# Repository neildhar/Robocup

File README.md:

Robocup
=======

Contains code for arduino robocup Robot as well as schematics for the custom PCBs.

Please ensure that you leave sensible messages when you commit so that other people don't have to decipher them.

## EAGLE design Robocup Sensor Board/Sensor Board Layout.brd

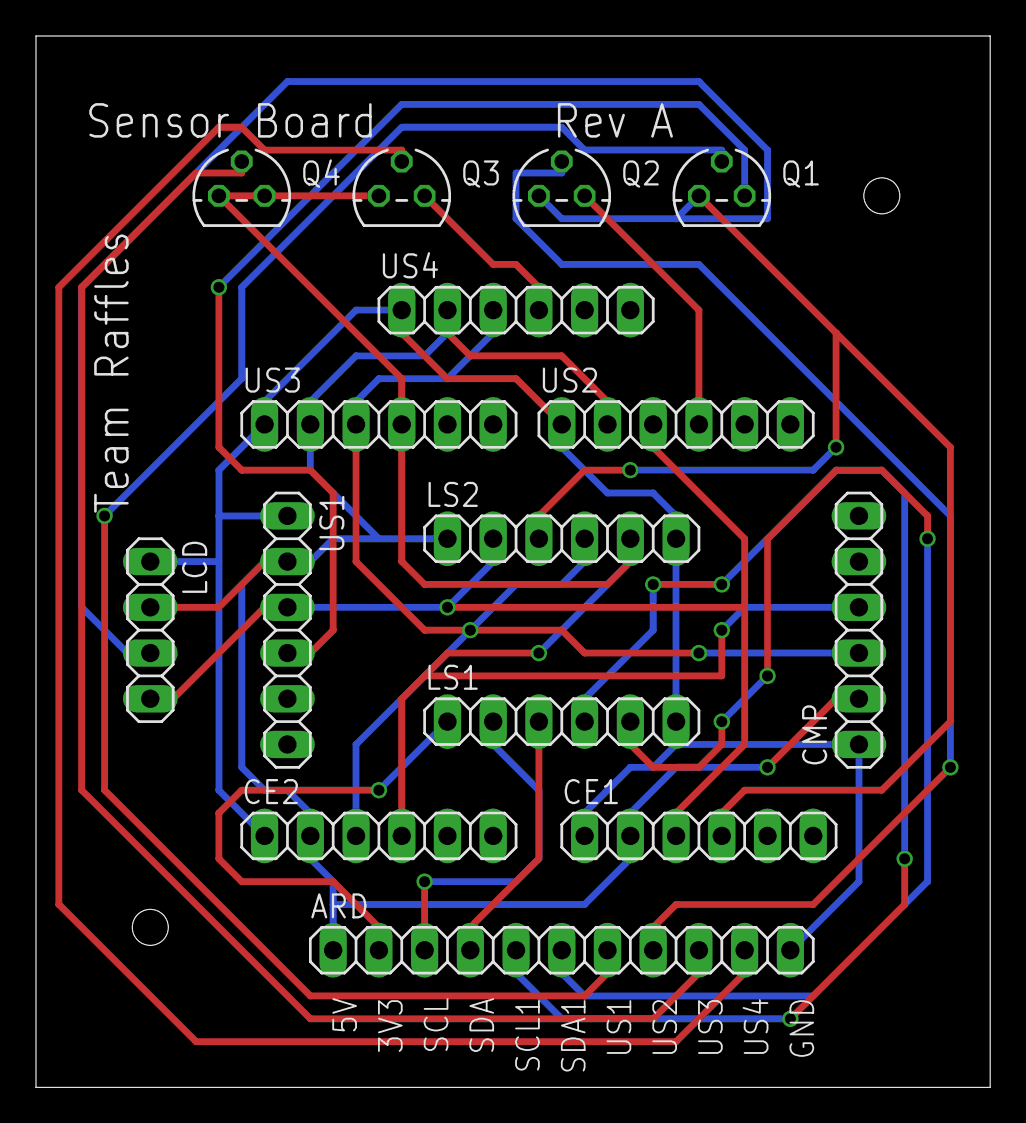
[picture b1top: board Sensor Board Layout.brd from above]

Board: 4 copper layers, 53.0 x 58.4 mm, 15 parts (0 on the bottom side), 18 nets.

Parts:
ARD: 1X11
CE1, CE2: 1X06
CMP: 1X06
LCD: 1X04
LS1, LS2: 1X06
Q1, Q2, Q3, Q4: TO-92
US1, US2, US3, US4: 1X06

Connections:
+3V3: ARD.2, LS1.1
+5V: ARD.1, CE1.2, CE2.2, CMP.2, LCD.2, LS2.1, US1.2, US2.2, US3.2, US4.2
GND: ARD.11, CE1.1, CE2.1, CMP.1, LCD.1, LS1.6, LS2.6, US1.1, US2.1, US3.1, US4.1
unnamed: Q1.3, US1.4
unnamed: Q2.3, US2.4
unnamed: Q3.3, US4.4
SCL1H: CE2.3, CMP.3, LS2.4, US3.3, US4.3
SCL1L: ARD.5, LS1.4
SCLH: CE1.3, LCD.4, LS2.2, US1.3, US2.3
SCLL: ARD.3, LS1.2
SDA1H: CE2.4, CMP.4, LS2.5, Q3.1, Q4.1, Q4.3, US3.4
SDA1L: ARD.6, LS1.5
SDAH: CE1.4, LCD.3, LS2.3, Q1.1, Q2.1
SDAL: ARD.4, LS1.3
US1E: ARD.7, Q1.2
US2E: ARD.8, Q2.2
US3E: ARD.9, Q4.2
US4E: ARD.10, Q3.2

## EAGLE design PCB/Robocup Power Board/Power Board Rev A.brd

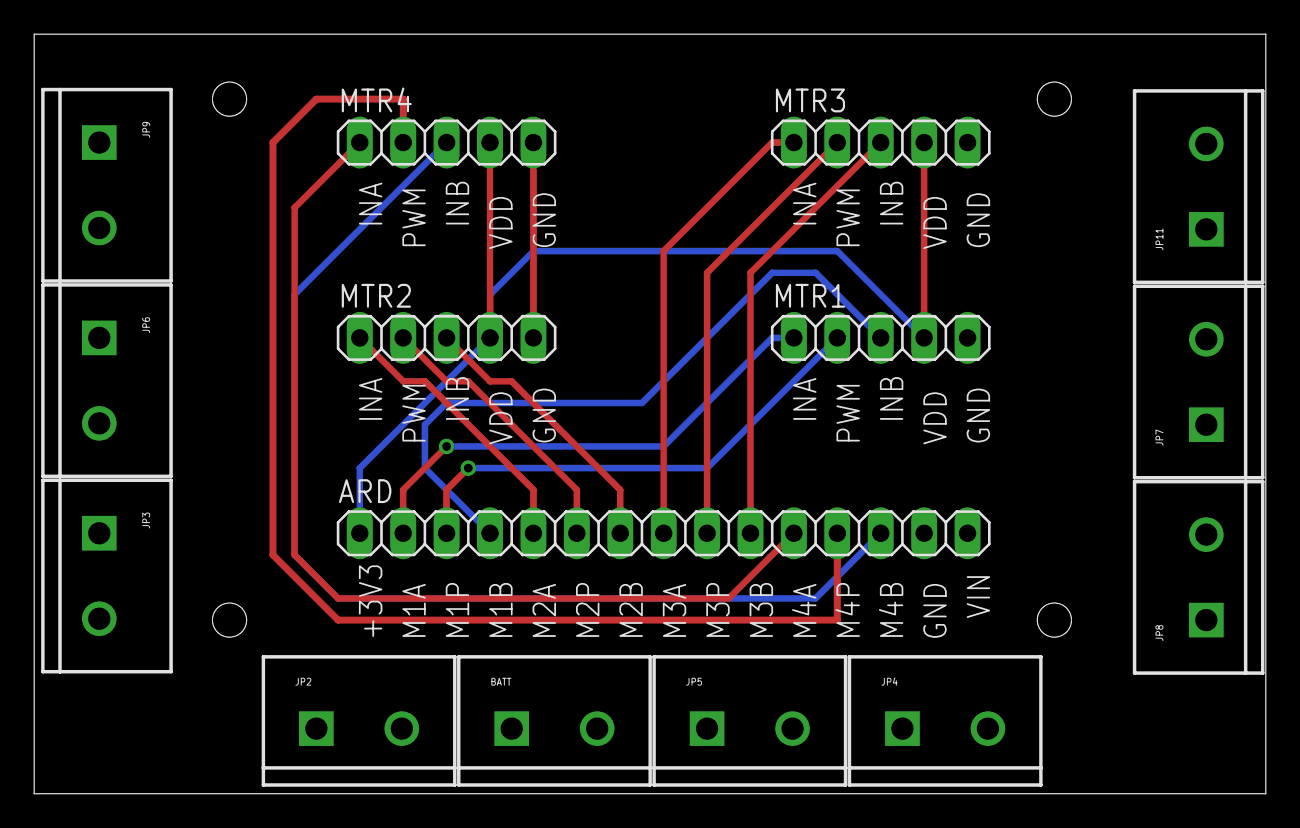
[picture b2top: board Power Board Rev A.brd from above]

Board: 2 copper layers, 72.1 x 44.4 mm, 15 parts (0 on the bottom side), 15 nets.

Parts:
ARD: 1X15
BATT: M025MM; SCREWTERMINAL-5MM-2
JP2, JP3, JP4, JP5, JP6, JP7, JP8, JP9, JP11: M025MM; SCREWTERMINAL-5MM-2
MTR1, MTR2, MTR3, MTR4: 1X05

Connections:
+3V3: ARD.1, MTR1.4, MTR2.4, MTR3.4, MTR4.4
GND: ARD.14, BATT.2, JP2.2, JP3.2, JP4.2, JP5.2, JP6.2, JP7.2, JP8.2, JP9.2, JP11.2, MTR1.5, MTR2.5, MTR3.5, MTR4.5
unnamed: ARD.2, MTR1.1
unnamed: ARD.3, MTR1.2
unnamed: ARD.4, MTR1.3
unnamed: ARD.5, MTR2.1
unnamed: ARD.6, MTR2.2
unnamed: ARD.7, MTR2.3
unnamed: ARD.8, MTR3.1
unnamed: ARD.9, MTR3.2
unnamed: ARD.10, MTR3.3
unnamed: ARD.11, MTR4.1
unnamed: ARD.13, MTR4.3
S$1: ARD.12, MTR4.2
VCC: ARD.15, BATT.1, JP2.1, JP3.1, JP4.1, JP5.1, JP6.1, JP7.1, JP8.1, JP9.1, JP11.1

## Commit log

2014-05-13 Fixed bug in reading compound eye
    Changed the mistake where the code sent the wrong command to the
    compound eye
2014-05-13 Restructuring
    Cleaned up folder structure, time to get organised
2014-05-13 Revert "Update Diagnostics.ino"
    This reverts commit 02557d601f0c8b267abc5f2daa6de15f704be76e.
2014-05-13 Restructured
    A little more sorting out
2014-05-13 Created Readme.md
2014-05-13 Added Symlinks to simplify editing of libraries
    If creating new libraries, contact Neil so he can link them up
    appropriately.
    Symlinks mean that editing the libraries for diagnostics edits them for
    the main code and vice versa. Keeps the code tidy. Please note that
    this code will fall apart on non-UNIX systems :P
2014-05-14 Added compass library
    Compass library and relevant symlinks added. Please remember to include
    the library in your code :)
2014-05-19 Added zero reset & removed symlinking
2014-05-19 Some restructuring
2014-05-29 Updated CMPS10 Library
    Library now includes magnetometer reading
2014-05-30 Updated the diagnostics and Main program
    Somewhat working
2014-05-30 Removed ABS
    Code is now ABS-free
2014-05-30 Changed CA_kd
2014-12-07 Added comments, updated compass reset
    More details in comments. Compass reset now interactive.
2015-01-26 Updated I2C Bus for compass
    I2C bus for compass changed to account for PCB design.
2015-02-06 Fixed unknown bug
    Main code was not working at all so it was replaced with Diagnostics.
2015-02-13 Motor power increased
    Speed of motors raised due to low robot speed. Minor adjustments made
    to the programme as well.
2015-04-17 Minor Updates
    Still not working
2015-04-20 Initial commit From https://github.com/Jimboker/Robocup
2015-04-20 Serial compass library added
    UNTESTED Serial compass library incorporated into the Diagnostics folder
2015-04-21 Cleanup of Serial Library and Initialise compass
2015-04-21 Serial compass improvements implemented high baud rate function init(baudRate) replaced serial class with hardwareSerial
2015-04-21 Implement split magRead magRead1() sends read request magRead2() reads from buffer and returns value Place magRead1 in start of program, magRead2 after program logic/ultrasound reads
2015-04-21 Cleanup and Minor Changes
2015-04-22 Working Code
2015-04-22 Implement PID compass align
2015-04-22 Added in tentative PID compass code
2015-04-23 Minor Changes
2015-04-24 Fixed compass, alternative vd speed control, broken though
2015-04-24 VD cannot do compass and movement at same time , suspecting non-linear motor power
2015-07-04 Simplified code
    Functions are now more general purpose and code repetition has been
    minimised. This code is still UNTESTED.
2015-07-11 Streamlined libraries for Diagnostics
    Libraries are now more general purpose and more readable
2015-08-17 General neatening
    General neatening. More may follow
2015-08-17 Edited compass calibration and factory reset functions
    roll back changes if any issues crop up. The previous code didn’t make
    much sense though
2015-10-02 Changed init function for CMPS10_Serial
    init function is now called setBaud as it serves no other significant
    purpose and is thus not required.
2015-10-02 fixed comments
    fixed comments at the start of the CMPS10 libraries
2018-07-29 making public

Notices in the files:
parts and their libraries:
SparkFun-Connectors: Licensing: CC v3.0 Share-Alike You are welcome to use this library for commercial purposes.
